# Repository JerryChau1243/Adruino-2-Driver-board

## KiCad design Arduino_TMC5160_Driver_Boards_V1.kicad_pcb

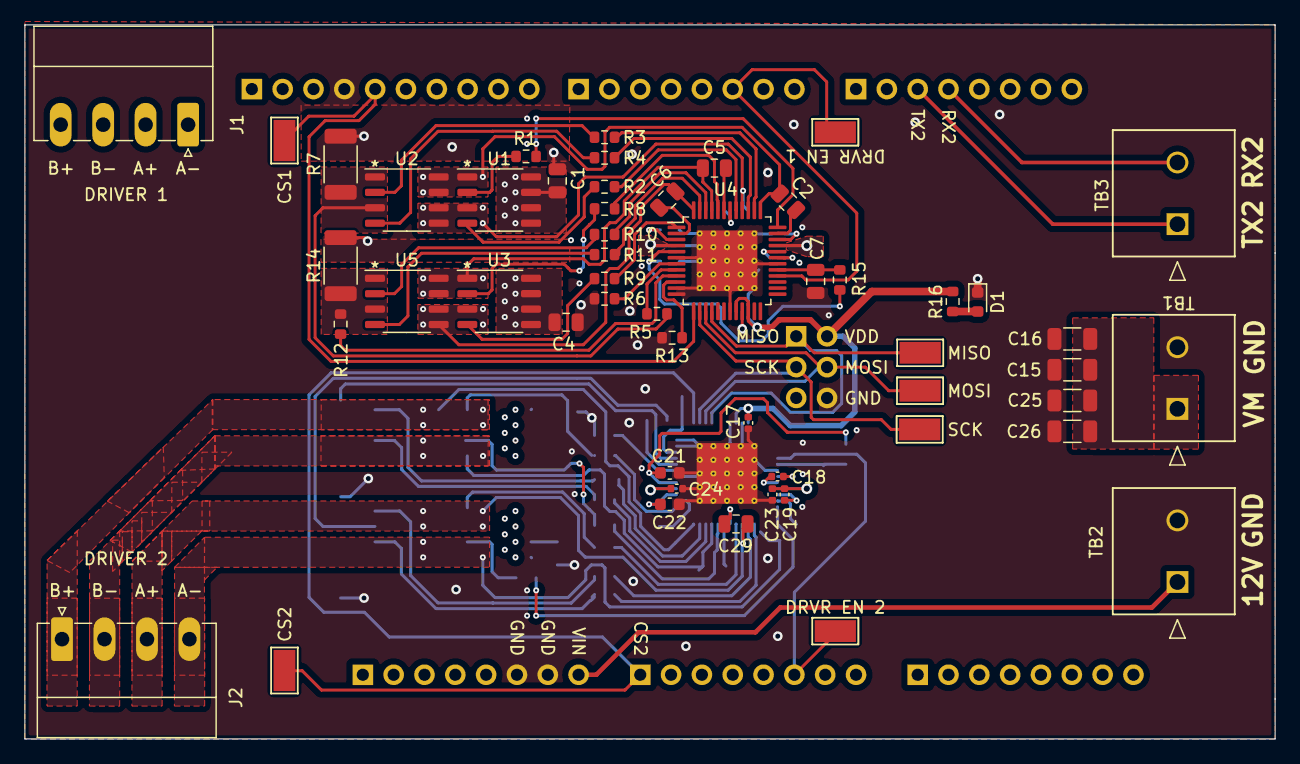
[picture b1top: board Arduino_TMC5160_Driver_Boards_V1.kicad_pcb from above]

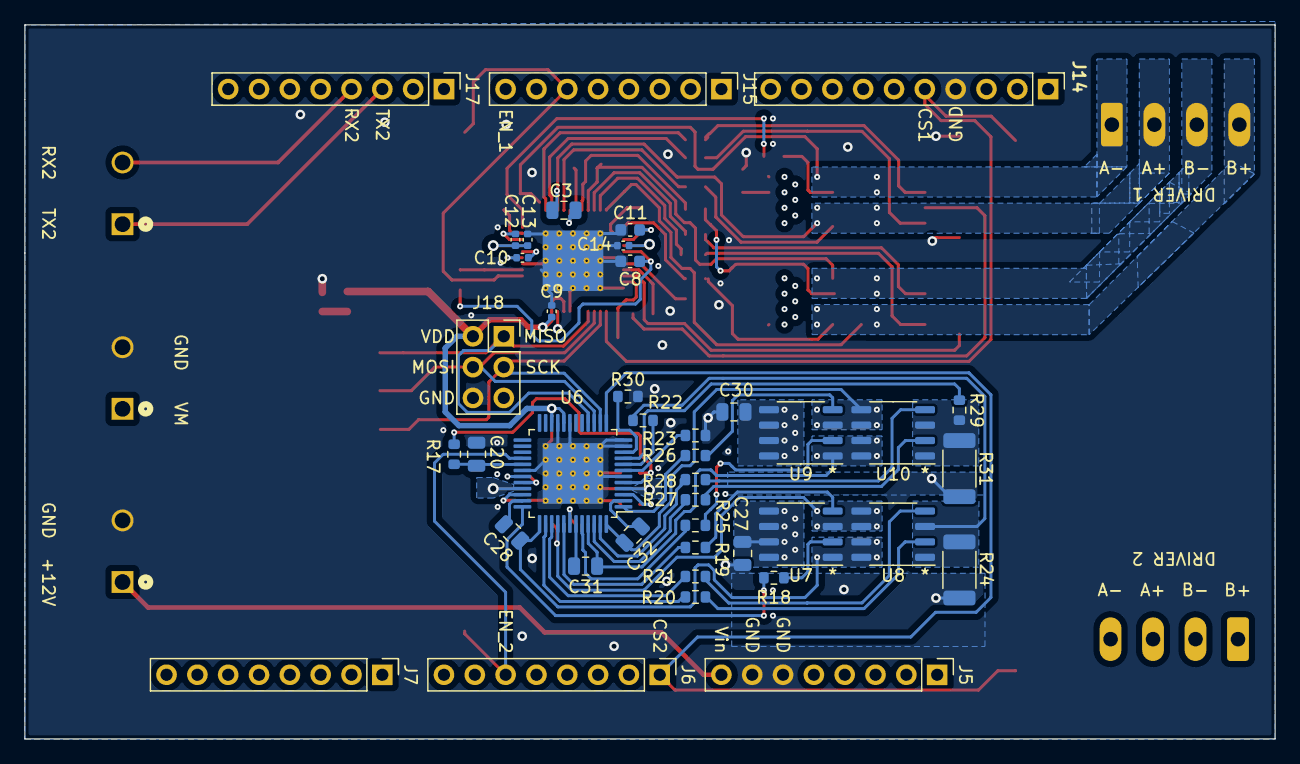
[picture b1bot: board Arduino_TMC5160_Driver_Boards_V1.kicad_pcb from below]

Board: 4 copper layers, 103.0 x 58.8 mm, 93 parts (41 on the bottom side), 86 nets.

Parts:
C1, C4, C7, C20, C27, C30: 470nF; C_0805_2012Metric
C2, C3, C5, C6, C28, C29, C31, C32: 220nF; C_0805_2012Metric
C8, C11, C21, C22: 2.2uF; C_0603_1608Metric
C9, C12, C13, C14, C17, C19, C23, C24: 100nF; C_0402_1005Metric
C10, C18: 22nF; C_0402_1005Metric
C15, C16, C25, C26: 10uF; C_1206_3216Metric
D1: GREEN; LED_0603_1608Metric
J1, J2: 2350514-4; P3.50mm_4POS_Right_TE
J5: Power; PinHeader_1x08_P2.54mm_Vertical
J6, J7: Analog; PinHeader_1x08_P2.54mm_Vertical
J14: Digital; PinHeader_1x10_P2.54mm_Vertical
J15: Digital; PinHeader_1x08_P2.54mm_Vertical
J17: Communication; PinHeader_1x08_P2.54mm_Vertical
J18: Conn_02x03_Odd_Even; PinSocket_2x03_P2.54mm_Vertical
R1, R2, R3, R4, R8, R9, R10, R11, R18, R19, R20, R21, R25, R26, R27, R28: 22; R_0603_1608Metric
R5, R6, R12, R13, R22, R23, R29, R30: 47; R_0603_1608Metric
R7, R14, R24, R31: 0.075; R_2010_5025Metric
R15, R17: 2.2; R_0603_1608Metric
R16: 1k; R_0603_1608Metric
TB1, TB2, TB3: 1715721; Screw_P5.08mm_2POS_PHX
TP1: MISO; TestPoint_Keystone_5015_Micro-Minature
TP2: MOSI; TestPoint_Keystone_5015_Micro-Minature
TP4: CLK; TestPoint_Keystone_5015_Micro-Minature
TP5: CS2; TestPoint_Keystone_5015_Micro-Minature
TP6: CS1; TestPoint_Keystone_5015_Micro-Minature
TP7: DRV_EN_2; TestPoint_Keystone_5015_Micro-Minature
TP9: DRV_EN_1; TestPoint_Keystone_5015_Micro-Minature
U1, U2, U3, U5, U7, U8, U9, U10: AO4882; SOP-8_3.9x4.9mm_P1.27mm
U4, U6: TMC5160A-TA; TQFP-48-1EP_7x7mm_P0.5mm_EP5x5mm_ThermalVias

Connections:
+12V: J5.8, TB2.1
/CS1: J14.5, TP6.1, U4.13 (~CS/CFG3)
/CS2: J6.1, TP5.1, U6.13 (~CS/CFG3)
/DRV_ENN_1: J15.6, TP9.1, U4.28 (~DRV_EN)
/DRV_ENN_2: J6.6, TP7.1, U6.28 (~DRV_EN)
/H-Bridge/A+_1: C3.1, J1.2, U1.3 (S1), U2.5 (D1), U2.6 (D1), U4.40 (BMA1)
/H-Bridge/A-_1: C2.1, J1.1, U1.1 (S2), U2.7 (D2), U2.8 (D2), U4.37 (BMA2)
/H-Bridge/B+_1: C6.1, J1.4, U3.3 (S1), U4.48 (BMB1), U5.5 (D1), U5.6 (D1)
/H-Bridge/B-_1: C5.1, J1.3, U3.1 (S2), U4.45 (BMB2), U5.7 (D2), U5.8 (D2)
/H-Bridge/CA_1: C3.2, U4.42 (CA1)
/H-Bridge/CA_2: C2.2, U4.35 (CA2)
/H-Bridge/CB_1: C6.2, U4.2 (CB1)
/H-Bridge/CB_2: C5.2, U4.43 (CB2)
/H-Bridge/HA_1: R2.2, U4.41 (HA1)
/H-Bridge/HA_2: R1.1, U4.36 (HA2)
/H-Bridge/HB_1: R9.2, U4.1 (HB1)
/H-Bridge/HB_2: R8.1, U4.44 (HB2)
/H-Bridge/LA_1: R4.2, U4.39 (LA1)
/H-Bridge/LA_2: R3.1, U4.38 (LA2)
/H-Bridge/LB_1: R11.2, U4.47 (LB1)
/H-Bridge/LB_2: R10.1, U4.46 (LB2)
/H-Bridge/SRAH: R5.1, U4.8 (SRAH)
/H-Bridge/SRAL: R6.2, U4.7 (SRAL)
/H-Bridge/SRBH: R12.1, U4.9 (SRBH)
/H-Bridge/SRBL: R13.2, U4.10 (SRBL)
/H-Bridge_2/A+_2: C29.1, J2.3, U6.40 (BMA1), U7.3 (S1), U8.5 (D1), U8.6 (D1)
/H-Bridge_2/A-_2: C28.1, J2.4, U6.37 (BMA2), U7.1 (S2), U8.7 (D2), U8.8 (D2)
/H-Bridge_2/B+_2: C32.1, J2.1, U6.48 (BMB1), U9.3 (S1), U10.5 (D1), U10.6 (D1)
/H-Bridge_2/B-_2: C31.1, J2.2, U6.45 (BMB2), U9.1 (S2), U10.7 (D2), U10.8 (D2)
/H-Bridge_2/CA_1: C29.2, U6.42 (CA1)
/H-Bridge_2/CA_2: C28.2, U6.35 (CA2)
/H-Bridge_2/CB_1: C32.2, U6.2 (CB1)
/H-Bridge_2/CB_2: C31.2, U6.43 (CB2)
/H-Bridge_2/HA_1: R19.2, U6.41 (HA1)
/H-Bridge_2/HA_2: R18.1, U6.36 (HA2)
/H-Bridge_2/HB_1: R26.2, U6.1 (HB1)
/H-Bridge_2/HB_2: R25.1, U6.44 (HB2)
/H-Bridge_2/LA_1: R21.2, U6.39 (LA1)
/H-Bridge_2/LA_2: R20.1, U6.38 (LA2)
/H-Bridge_2/LB_1: R28.2, U6.47 (LB1)
/H-Bridge_2/LB_2: R27.1, U6.46 (LB2)
/H-Bridge_2/SRAH: R22.1, U6.8 (SRAH)
/H-Bridge_2/SRAL: R23.2, U6.7 (SRAL)
/H-Bridge_2/SRBH: R29.1, U6.9 (SRBH)
/H-Bridge_2/SRBL: R30.2, U6.10 (SRBL)
/MISO: J18.1, TP1.1, U4.16 (SDO/CFG0), U6.16 (SDO/CFG0)
/MOSI: J18.4, TP2.1, U4.15 (SDI/CFG1), U6.15 (SDI/CFG1)
/SCK: J18.3, TP4.1, U4.14 (SCK/CFG2), U6.14 (SCK/CFG2)
/Untitled Sheet/RX2: J17.4, TB3.2
/Untitled Sheet/TX2: J17.3, TB3.1
GND: C1.2, C4.2, C7.2, C8.2, C9.2, C11.2, C13.2, C14.2, C15.2, C16.2, C17.2, C20.2, C21.2, C22.2, C23.2, C24.2, C25.2, C26.2, C27.2, C30.2, D1.1 (K), J5.6, J5.7, J14.4, J18.6, R6.1, R7.1, R13.1, R14.1, R23.1, R24.1, R30.1, R31.1, TB1.2, TB2.2, U4.6 (GNDA), U4.11 (TST_MODE), U4.12 (CLK), U4.19 (GNDD), U4.21 (SD_MODE), U4.30 (GNDD), U4.49 (EP), U6.6 (GNDA), U6.11 (TST_MODE), U6.12 (CLK), U6.19 (GNDD), U6.21 (SD_MODE), U6.30 (GNDD), U6.49 (EP)
unnamed: D1.2 (A), R16.2
unnamed: R2.1, U1.4 (G1)
unnamed: R1.2, U1.2 (G2)
unnamed: R4.1, U2.4 (G1)
unnamed: R3.2, U2.2 (G2)
unnamed: R5.2, R7.2, U2.1 (S2), U2.3 (S1)
unnamed: R9.1, U3.4 (G1)
unnamed: R8.2, U3.2 (G2)
unnamed: C8.1, R15.2, U4.5 (5VOUT)
unnamed: C11.1, U4.3 (12VOUT)
unnamed: C10.2, U4.32 (CPI)
unnamed: C10.1, U4.31 (CPO)
unnamed: C7.1, R15.1, U4.29 (VCC)
unnamed: C12.2, U4.34 (VCP)
unnamed: R11.1, U5.4 (G1)
unnamed: R10.2, U5.2 (G2)
unnamed: R12.2, R14.2, U5.1 (S2), U5.3 (S1)
unnamed: C21.1, R17.2, U6.5 (5VOUT)
unnamed: C22.1, U6.3 (12VOUT)
unnamed: C18.2, U6.32 (CPI)
unnamed: C18.1, U6.31 (CPO)
unnamed: C20.1, R17.1, U6.29 (VCC)
unnamed: C19.2, U6.34 (VCP)
unnamed: R19.1, U7.4 (G1)
unnamed: R18.2, U7.2 (G2)
unnamed: R21.1, U8.4 (G1)
unnamed: R20.2, U8.2 (G2)
unnamed: R22.2, R24.2, U8.1 (S2), U8.3 (S1)
unnamed: R26.1, U9.4 (G1)
unnamed: R25.2, U9.2 (G2)
unnamed: R28.1, U10.4 (G1)
unnamed: R27.2, U10.2 (G2)
unnamed: R29.2, R31.2, U10.1 (S2), U10.3 (S1)
VDD: C9.1, C17.1, J18.2, R16.1, U4.20 (VCC_IO), U4.22 (SPI_MODE), U6.20 (VCC_IO), U6.22 (SPI_MODE)
Vdrive: C1.1, C4.1, C12.1, C13.1, C14.1, C15.1, C16.1, C19.1, C23.1, C24.1, C25.1, C26.1, C27.1, C30.1, TB1.1, U1.5 (D1), U1.6 (D1), U1.7 (D2), U1.8 (D2), U3.5 (D1), U3.6 (D1), U3.7 (D2), U3.8 (D2), U4.4 (VSA), U4.33 (VS), U6.4 (VSA), U6.33 (VS), U7.5 (D1), U7.6 (D1), U7.7 (D2), U7.8 (D2), U9.5 (D1), U9.6 (D1), U9.7 (D2), U9.8 (D2)
